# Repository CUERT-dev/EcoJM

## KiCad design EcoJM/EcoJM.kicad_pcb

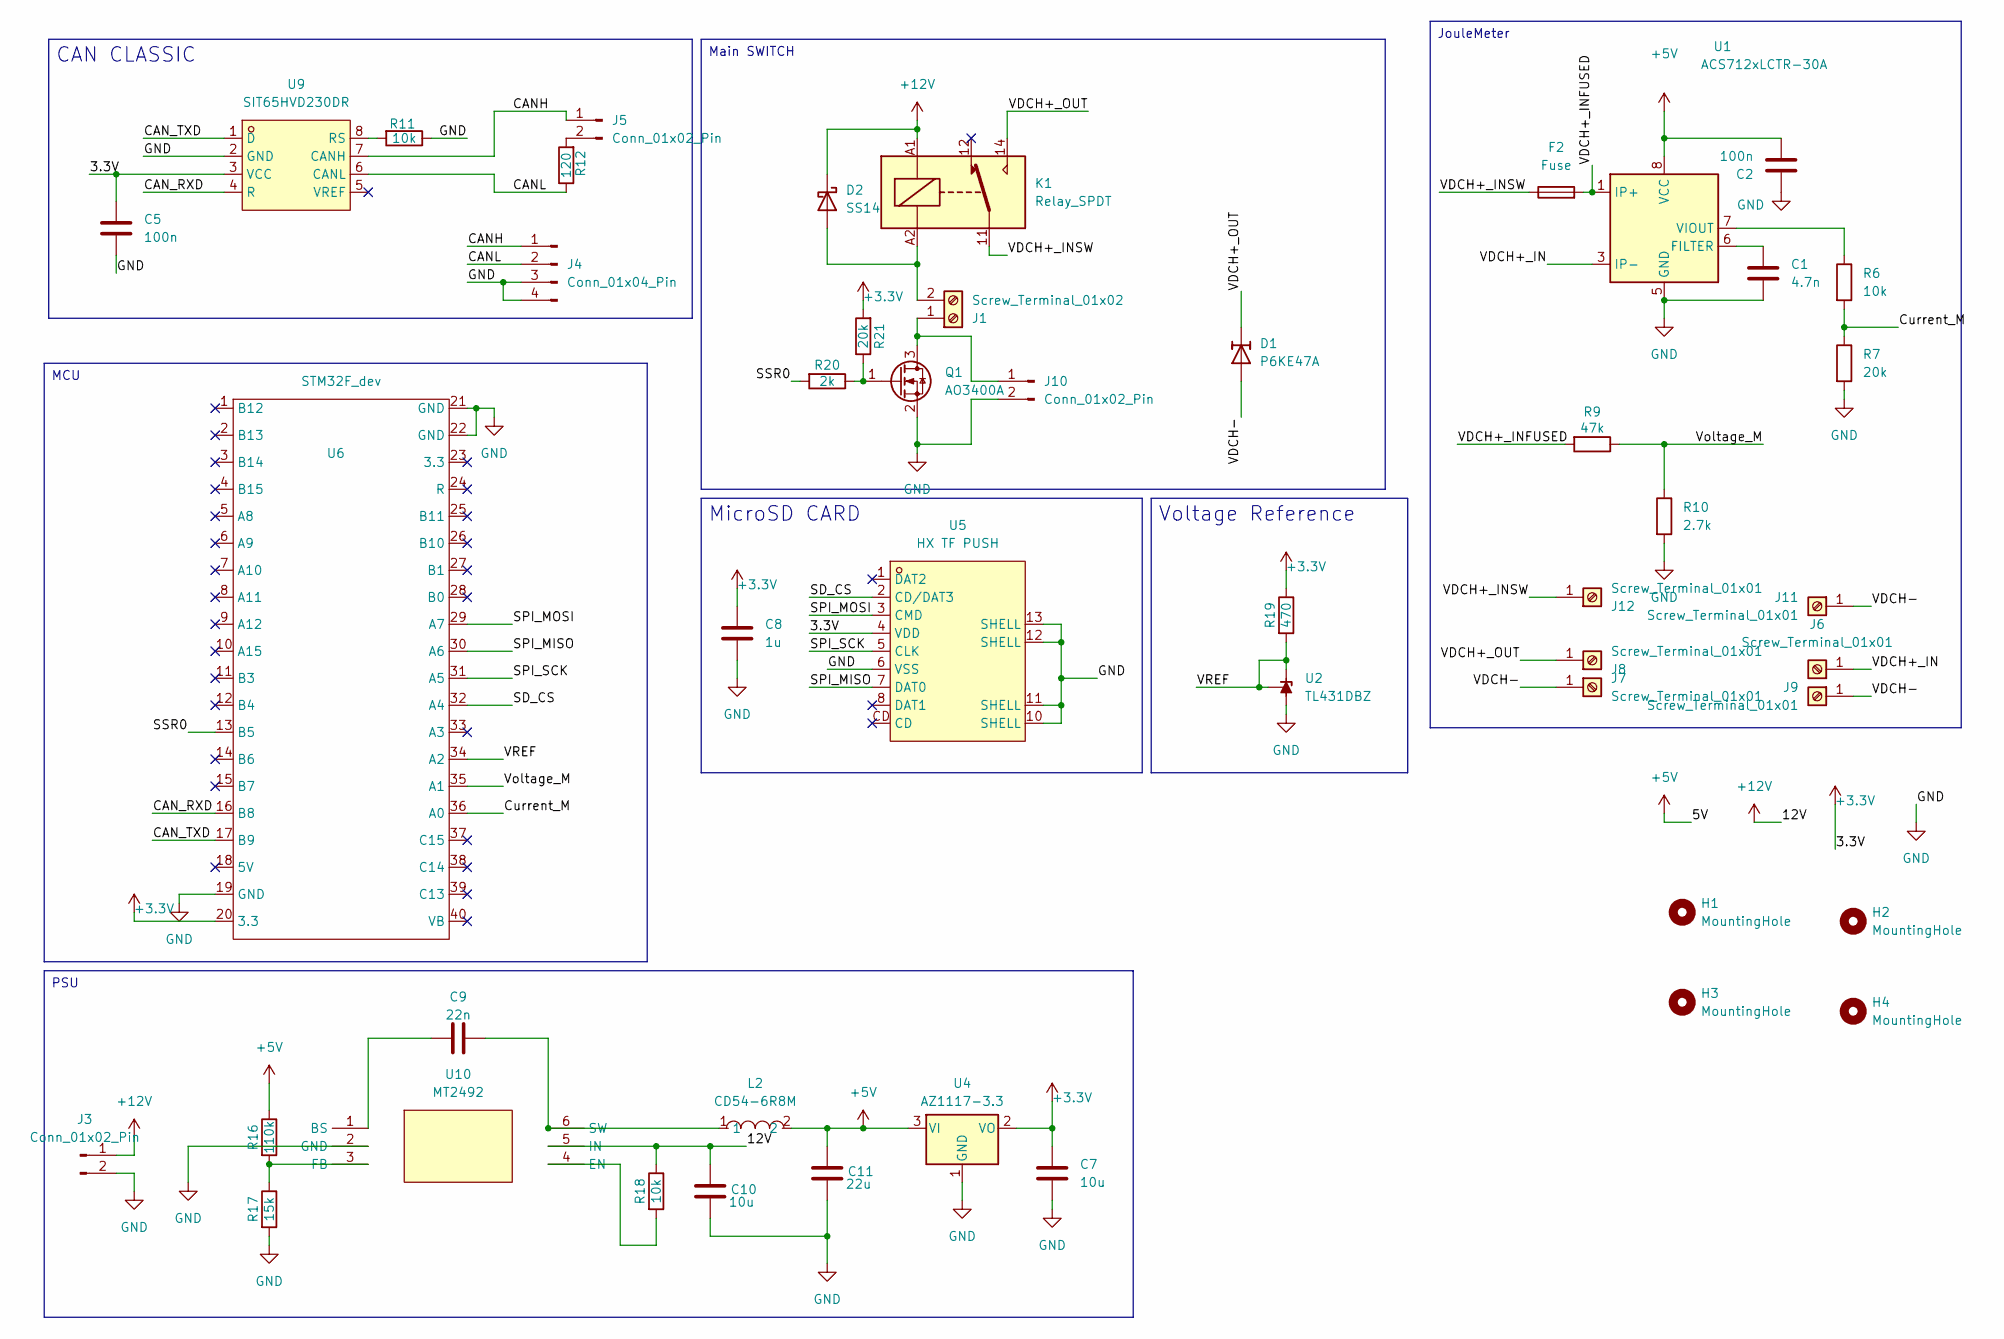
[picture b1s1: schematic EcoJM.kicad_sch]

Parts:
C1: 4.7n; C_0603_1608Metric_Pad1.08x0.95mm_HandSolder
C2, C5: 100n; C_0603_1608Metric_Pad1.08x0.95mm_HandSolder
C7, C10: 10u; C_1206_3216Metric_Pad1.33x1.80mm_HandSolder
C8: 1u; C_0603_1608Metric_Pad1.08x0.95mm_HandSolder
C9: 22n; C_0603_1608Metric_Pad1.08x0.95mm_HandSolder
C11: 22u; C_1206_3216Metric_Pad1.33x1.80mm_HandSolder
D1: P6KE47A; D_DO-15_P10.16mm_Horizontal
D2: SS14; D_SMA
F2: Fuse; Fuseholder_Clip-5x20mm_Littelfuse_520_Inline_P20.50x5.80mm_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
H1, H2, H3, H4: MountingHole; MountingHole_3.2mm_M3_DIN965
J1: Screw_Terminal_01x02; TerminalBlock_Phoenix_MKDS-1,5-2_1x02_P5.00mm_Horizontal
J3: Conn_01x02_Pin; JST_XH_B2B-XH-A_1x02_P2.50mm_Vertical
J4: Conn_01x04_Pin; JST_XH_B4B-XH-A_1x04_P2.50mm_Vertical
J5, J10: Conn_01x02_Pin; PinHeader_1x02_P2.54mm_Vertical
J6, J7, J8, J9: Screw_Terminal_01x01; M3_PCONN_1x01
J11, J12: Screw_Terminal_01x01; SolderWire-0.25sqmm_1x01_D0.65mm_OD1.7mm_Relief
K1: Relay_SPDT; T91 30A
L2: CD54-6R8M; IND-SMD_L5.8-W5.2_CD54; MPN CD54-6R8M; LCSC Part C7588992
Q1: AO3400A; SOT-23
R6, R11: 10k; C_0603_1608Metric_Pad1.08x0.95mm_HandSolder
R7: 20k; C_0603_1608Metric_Pad1.08x0.95mm_HandSolder
R9: 47k; R_1206_3216Metric_Pad1.30x1.75mm_HandSolder
R10: 2.7k; R_1206_3216Metric_Pad1.30x1.75mm_HandSolder
R12: 120; R_1206_3216Metric_Pad1.30x1.75mm_HandSolder
R16: 110k; R_0603_1608Metric_Pad0.98x0.95mm_HandSolder
R17: 15k; R_0603_1608Metric_Pad0.98x0.95mm_HandSolder
R18: 10k; R_0603_1608Metric_Pad0.98x0.95mm_HandSolder
R19: 470; R_0603_1608Metric_Pad0.98x0.95mm_HandSolder
R20: 2k; R_0603_1608Metric_Pad0.98x0.95mm_HandSolder
R21: 20k; R_0603_1608Metric_Pad0.98x0.95mm_HandSolder
U1: ACS712xLCTR-30A; SOIC-8_3.9x4.9mm_P1.27mm
U2: TL431DBZ; SOT-23
U4: AZ1117-3.3; SOT-89-3_Handsoldering
U5: HX TF PUSH; TF-SMD_TF-PUSH; MPN HX TF PUSH; LCSC Part C5184837
U6: STM32F_dev; STM32F_devboard
U9: SIT65HVD230DR; SOP-8_L4.9-W3.9-P1.27-LS6.0-BL; MPN SIT65HVD230DR; LCSC Part C496619
U10: MT2492; SOT-23-6_L2.9-W1.6-P0.95-LS2.8-BL_3; MPN MT2492; LCSC Part C89358

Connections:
+3.3V: C5.1, C7.1, C8.1, R19.1, R21.2, U4.2 (VO), U5.4 (VDD), U6.20 (3.3), U9.3 (VCC)
+5V: C2.2, C11.1, L2.2, R16.1, U1.8 (VCC), U4.3 (VI); also elsewhere on the board
+12V: C10.1, D2.1 (K), J3.1, K1.A1, R18.1, U10.5 (IN)
/CANH: J4.1, J5.1, U9.7 (CANH)
/CANL: J4.2, R12.1, U9.6 (CANL)
/CAN_RXD: U6.16 (B8), U9.4 (R)
/CAN_TXD: U6.17 (B9), U9.1 (D)
/Current_M: R6.2, R7.1, U6.36 (A0)
/SD_CS: U5.2 (CD/DAT3), U6.32 (A4)
/SPI_MISO: U5.7 (DAT0), U6.30 (A6)
/SPI_MOSI: U5.3 (CMD), U6.29 (A7)
/SPI_SCK: U5.5 (CLK), U6.31 (A5)
/SSR0: R20.2, U6.13 (B5)
/VDCH+_IN: J6.1 (Pin_1_1), U1.3 (IP-), U1.4 (IP-)
/VDCH+_INFUSED: F2.2, R9.2, U1.1 (IP+), U1.2 (IP+)
/VDCH+_INSW: F2.1, J12.1 (Pin_1_1), K1.11
/VDCH+_OUT: D1.1 (K), J8.1 (Pin_1_1), K1.14
/VDCH-: D1.2 (A), J7.1 (Pin_1_1), J9.1 (Pin_1_1), J11.1 (Pin_1_1)
/VREF: R19.2, U2.1 (K), U2.2 (REF), U6.34 (A2)
/Voltage_M: R9.1, R10.1, U6.35 (A1)
GND: C1.2, C2.1, C5.2, C7.2, C8.2, C10.2, C11.2, J3.2, J4.3, J4.4, J10.2, Q1.2 (S), R7.2, R10.2, R11.1, R17.2, U1.5 (GND), U2.3 (A), U4.1 (GND), U5.6 (VSS), U5.10 (SHELL), U5.11 (SHELL), U5.12 (SHELL), U5.13 (SHELL), U6.19 (GND), U6.21 (GND), U6.22 (GND), U9.2 (GND), U10.2 (GND); also elsewhere on the board
unnamed: D2.2 (A), J1.2, K1.A2
unnamed: J1.1, J10.1, Q1.3 (D)
unnamed: J5.2, R12.2
unnamed: Q1.1 (G), R20.1, R21.1
unnamed: C1.1, U1.6 (FILTER)
unnamed: R6.1, U1.7 (VIOUT)
unnamed: R11.2, U9.8 (RS)
unnamed: C9.2, U10.1 (BS)
unnamed: R18.2, U10.4 (EN)
unnamed: R16.2, R17.1, U10.3 (FB)
unnamed: C9.1, L2.1, U10.6 (SW)

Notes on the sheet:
MicroSD CARD
CAN CLASSIC
Main SWITCH
MCU
JouleMeter
PSU
Voltage Reference

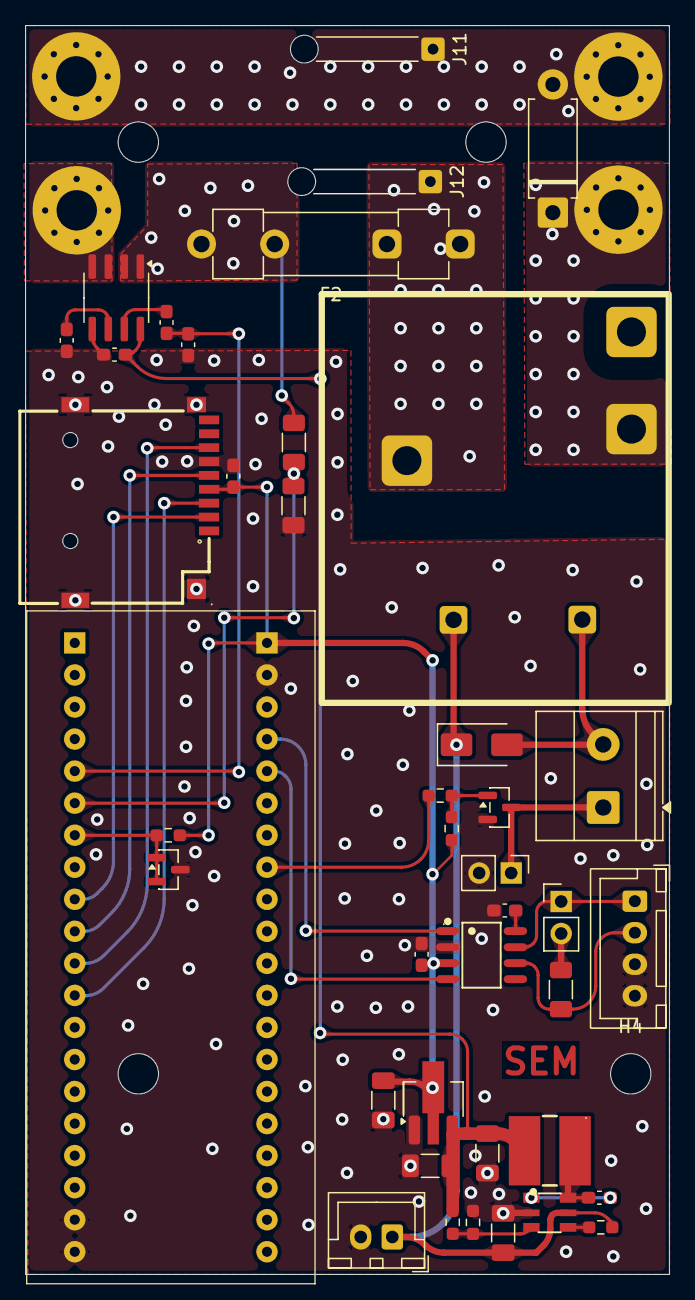
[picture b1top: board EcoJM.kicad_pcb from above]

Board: 2 copper layers, 51.0 x 99.0 mm, 49 parts (0 on the bottom side), 32 nets.

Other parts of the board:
C9#2: 22u; C_1206_3216Metric_Pad1.33x1.80mm_HandSolder

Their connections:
+5V: C9#2.1; also elsewhere on the board
GND: C9#2.2; also elsewhere on the board

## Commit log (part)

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2026-02-12 init
2026-02-12 bahr updoad
2026-02-13 STM_DEV done
    STM_DEV done
2026-02-14 sry forgot to save schematic xD
    sry forgot to save schematic xD
2026-02-14 Schematic = 100% , Footprints=100%
2026-02-14 Updates
    R variable added to op amp
    Buck converter V division Resistors values added
2026-02-15 Schematic REV by OMAR_MAGDY , REV0 Layout 80%
2026-02-18 Routing Finished
    bhbk ya Omar ya Magdy
2026-02-18 nseet a3ml save
    sorry
